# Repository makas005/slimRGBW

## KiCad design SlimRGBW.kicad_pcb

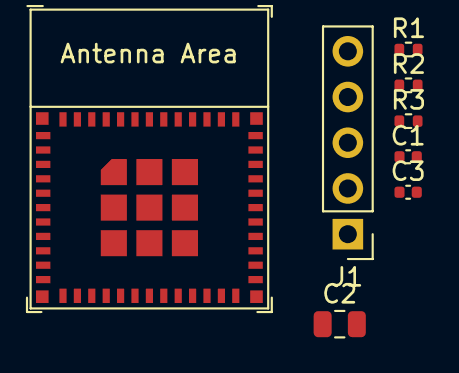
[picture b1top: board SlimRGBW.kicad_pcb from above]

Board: 2 copper layers, 8 parts (0 on the bottom side), 8 nets, no tracks yet.

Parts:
C1, C3: 100n; C_0402_1005Metric
C2: 10u; C_0805_2012Metric
J1: Conn_01x05_Pin; PinHeader_1x05_P2.54mm_Vertical
R1: 100k; R_0402_1005Metric
R2, R3: 10k; R_0402_1005Metric
U1: ESP32-C3-MINI-1

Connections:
+3.3V: C2.1, C3.1, J1.1, R2.1, R3.1, U1.3 (3V3)
GND: C1.2, C2.2, C3.2, J1.5, U1.1 (GND), U1.2 (GND), U1.11 (GND), U1.14 (GND), U1.36 (GND), U1.37 (GND), U1.38 (GND), U1.39 (GND), U1.40 (GND), U1.41 (GND), U1.42 (GND), U1.43 (GND), U1.44 (GND), U1.45 (GND), U1.46 (GND), U1.47 (GND), U1.48 (GND), U1.49 (GND), U1.50 (GND), U1.51 (GND), U1.52 (GND), U1.53 (GND)
unnamed: J1.2, U1.31 (GPIO21/U0TXD)
unnamed: J1.3, U1.30 (GPIO20/U0RXD)
unnamed: J1.4, U1.23 (GPIO9)
unnamed: C1.1, U1.8 (EN/CHIP_PU)
unnamed: R2.2, U1.5 (GPIO2/ADC1_CH2)
unnamed: R3.2, U1.22 (GPIO8)

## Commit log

2025-12-19 add license
2026-01-17 Add mosfets to schematic, no footprint yet
